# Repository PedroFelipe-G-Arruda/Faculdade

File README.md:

# Faculdade
Matérias e programas desenvolvidos no meu 6° semestre de Engenharia da Computação.

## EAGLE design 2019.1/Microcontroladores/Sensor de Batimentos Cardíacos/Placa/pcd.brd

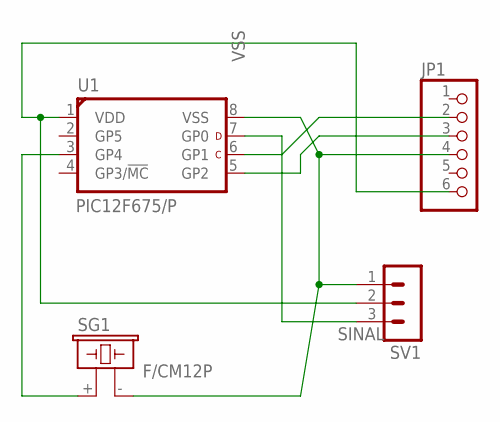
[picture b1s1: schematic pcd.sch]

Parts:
JP1: PINHD-1X6; 1X06
SG1: F/CM12P
SV1: MA03-1
U1: PIC12F675/P; DIL8-P

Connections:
unnamed: JP1.2, U1.6 (GP1)
unnamed: SG1.+ (1), U1.3 (GP4)
unnamed: JP1.3, U1.5 (GP2)
SINAL: SV1.3, U1.7 (GP0)
VDD: JP1.6, SV1.2, U1.1 (VDD)
VSS: JP1.4, SG1.- (2), SV1.1, U1.8 (VSS)

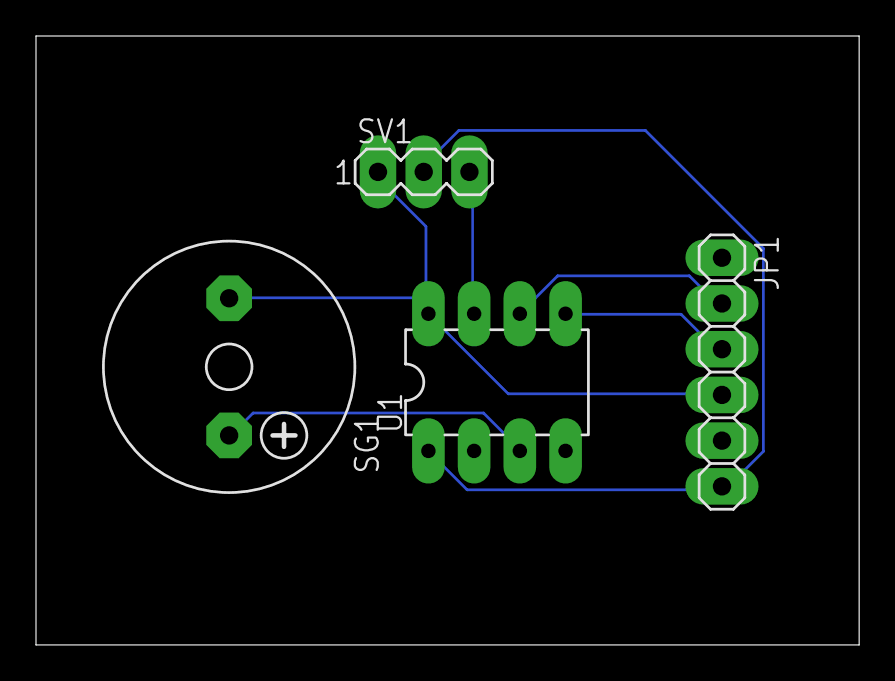
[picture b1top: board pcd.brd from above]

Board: 2 copper layers, 45.7 x 33.8 mm, 4 parts (0 on the bottom side), 6 nets.

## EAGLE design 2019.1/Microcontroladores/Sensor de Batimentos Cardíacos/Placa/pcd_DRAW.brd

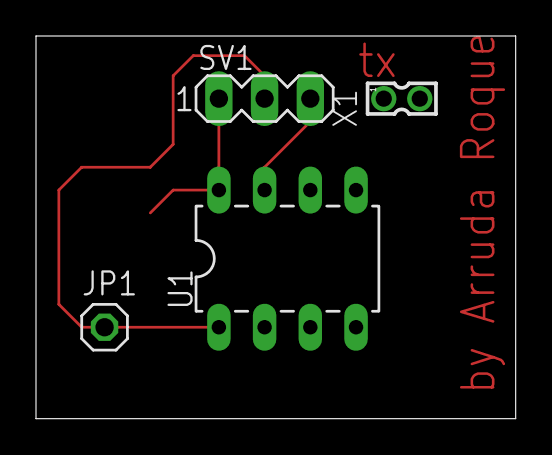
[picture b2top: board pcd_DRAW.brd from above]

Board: 2 copper layers, 26.6 x 21.3 mm, 4 parts (0 on the bottom side), 5 nets.

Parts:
JP1: 1X01
SV1: MA03-1
U1: PIC12F675/P; DIL8-P
X1: 87758-0216

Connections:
unnamed: U1.6, X1.1
unnamed: U1.5, X1.2
SINAL: SV1.3, U1.7
VDD: JP1.1, SV1.2, U1.1
VSS: SV1.1, U1.8

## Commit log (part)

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2018-08-14 Primeira tarefa
2018-08-14 Test
2018-08-14 Update programa01.py
    Programa que lê nomes de coloca em um arquivo de texto.
2018-08-14 Programa pronto
2018-08-14 Update README.md
    Estudande
2018-08-14 Aquivo com os nomes
2018-08-14 troca de nome do aquivo
2018-08-14 Atividades
2018-08-14 Nomes
2018-08-14 Programa conta linhas
2018-08-15 Programa fucionando mas não finalizado
2018-08-17 no message
2018-08-20 Não esta funcionando
2018-08-23 Programa Finalizado
2018-08-23 PRograma Automatos finalizado
2018-08-25 Rpgrama Finalizado
2018-09-05 Create LICENSE
2018-09-05 Gramatica
2018-09-12 Gramatica da linguagem 2
2018-09-12 Nova estrutura do FOR
2018-09-25 Programa usado na geração da gramatica
2018-09-25 Programa usado para fazer grafos
2018-10-12 Pronto ou quase
2018-10-13 Codigo finalizado
2018-10-26 Material LP2
2018-11-04 Analizador Lexico Finalizado
2018-11-04 Analizador Semantico Finalizado
2018-11-05 Analizador Sintatico Finalizado
2018-12-15 Codigo intermetiario/quase
2018-12-16 assembly 10%
2018-12-17 Rodando 98%
2019-02-26 Novo Semestre
2019-05-25 Bump tar from 2.2.1 to 2.2.2 in /2019.1/LP3/Ionic/Iapp01
    Bumps [tar](https://github.com/npm/node-tar) from 2.2.1 to 2.2.2.
    - [Release notes](https://github.com/npm/node-tar/releases)
    - [Commits](https://github.com/npm/node-tar/compare/v2.2.1...v2.2.2)
2019-05-31 Bump fstream from 1.0.11 to 1.0.12 in /2019.1/LP3/Ionic/Iapp01
    Bumps [fstream](https://github.com/npm/fstream) from 1.0.11 to 1.0.12.
    - [Release notes](https://github.com/npm/fstream/releases)
    - [Commits](https://github.com/npm/fstream/compare/v1.0.11...v1.0.12)
2019-12-29 Bump handlebars in /2019.1/LP3/Angular/my-project-name
    Bumps [handlebars](https://github.com/wycats/handlebars.js) from 4.1.2 to 4.5.3.
    - [Release notes](https://github.com/wycats/handlebars.js/releases)
    - [Changelog](https://github.com/wycats/handlebars.js/blob/master/release-notes.md)
    - [Commits](https://github.com/wycats/handlebars.js/compare/v4.1.2...v4.5.3)
2020-03-15 Bump acorn from 6.1.1 to 6.4.1 in /2019.1/LP3/Angular/my-project-name
    Bumps [acorn](https://github.com/acornjs/acorn) from 6.1.1 to 6.4.1.
    - [Release notes](https://github.com/acornjs/acorn/releases)
    - [Commits](https://github.com/acornjs/acorn/compare/6.1.1...6.4.1)
2020-06-07 Bump websocket-extensions in /2019.1/LP3/Angular/my-project-name
    Bumps [websocket-extensions](https://github.com/faye/websocket-extensions-node) from 0.1.3 to 0.1.4.
    - [Release notes](https://github.com/faye/websocket-extensions-node/releases)
    - [Changelog](https://github.com/faye/websocket-extensions-node/blob/master/CHANGELOG.md)
    - [Commits](https://github.com/faye/websocket-extensions-node/compare/0.1.3...0.1.4)
2020-07-07 Bump mixin-deep in /2019.1/LP3/Angular/my-project-name
    Bumps [mixin-deep](https://github.com/jonschlinkert/mixin-deep) from 1.3.1 to 1.3.2.
    - [Release notes](https://github.com/jonschlinkert/mixin-deep/releases)
    - [Commits](https://github.com/jonschlinkert/mixin-deep/compare/1.3.1...1.3.2)
2020-07-31 Bump elliptic from 6.4.1 to 6.5.3 in /2019.1/LP3/Angular/my-project-name
    Bumps [elliptic](https://github.com/indutny/elliptic) from 6.4.1 to 6.5.3.
    - [Release notes](https://github.com/indutny/elliptic/releases)
    - [Commits](https://github.com/indutny/elliptic/compare/v6.4.1...v6.5.3)
2020-09-10 Bump http-proxy in /2019.1/LP3/Angular/my-project-name
    Bumps [http-proxy](https://github.com/http-party/node-http-proxy) from 1.17.0 to 1.18.1.
    - [Release notes](https://github.com/http-party/node-http-proxy/releases)
    - [Changelog](https://github.com/http-party/node-http-proxy/blob/master/CHANGELOG.md)
    - [Commits](https://github.com/http-party/node-http-proxy/compare/1.17.0...1.18.1)
2021-03-30 Bump y18n from 4.0.0 to 4.0.1 in /2019.1/LP3/Angular/my-project-name
    Bumps [y18n](https://github.com/yargs/y18n) from 4.0.0 to 4.0.1.
    - [Release notes](https://github.com/yargs/y18n/releases)
    - [Changelog](https://github.com/yargs/y18n/blob/master/CHANGELOG.md)
    - [Commits](https://github.com/yargs/y18n/commits)
2021-04-30 Bump ssri from 6.0.1 to 6.0.2 in /2019.1/LP3/Angular/my-project-name
    Bumps [ssri](https://github.com/npm/ssri) from 6.0.1 to 6.0.2.
    - [Release notes](https://github.com/npm/ssri/releases)
    - [Changelog](https://github.com/npm/ssri/blob/v6.0.2/CHANGELOG.md)
    - [Commits](https://github.com/npm/ssri/compare/v6.0.1...v6.0.2)
2021-05-08 Bump url-parse in /2019.1/LP3/Angular/my-project-name
    Bumps [url-parse](https://github.com/unshiftio/url-parse) from 1.4.7 to 1.5.1.
    - [Release notes](https://github.com/unshiftio/url-parse/releases)
    - [Commits](https://github.com/unshiftio/url-parse/compare/1.4.7...1.5.1)
2021-05-09 Bump lodash in /2019.1/LP3/Angular/my-project-name
    Bumps [lodash](https://github.com/lodash/lodash) from 4.17.19 to 4.17.21.
    - [Release notes](https://github.com/lodash/lodash/releases)
    - [Commits](https://github.com/lodash/lodash/compare/4.17.19...4.17.21)
2021-05-27 Bump dns-packet in /2019.1/LP3/Angular/my-project-name
    Bumps [dns-packet](https://github.com/mafintosh/dns-packet) from 1.3.1 to 1.3.4.
    - [Release notes](https://github.com/mafintosh/dns-packet/releases)
    - [Changelog](https://github.com/mafintosh/dns-packet/blob/master/CHANGELOG.md)
    - [Commits](https://github.com/mafintosh/dns-packet/compare/v1.3.1...v1.3.4)
2021-08-04 Bump tar from 4.4.8 to 4.4.15 in /2019.1/LP3/Angular/my-project-name
    Bumps [tar](https://github.com/npm/node-tar) from 4.4.8 to 4.4.15.
    - [Release notes](https://github.com/npm/node-tar/releases)
    - [Changelog](https://github.com/npm/node-tar/blob/main/CHANGELOG.md)
    - [Commits](https://github.com/npm/node-tar/compare/v4.4.8...v4.4.15)
    ---
    updated-dependencies:
2021-09-01 Bump tar from 4.4.8 to 4.4.19 in /2019.1/LP3/Angular/my-project-name
    Bumps [tar](https://github.com/npm/node-tar) from 4.4.8 to 4.4.19.
    - [Release notes](https://github.com/npm/node-tar/releases)
    - [Changelog](https://github.com/npm/node-tar/blob/main/CHANGELOG.md)
    - [Commits](https://github.com/npm/node-tar/compare/v4.4.8...v4.4.19)
    ---
    updated-dependencies:
2021-10-06 Bump url-parse in /2019.1/LP3/Angular/my-project-name
    Bumps [url-parse](https://github.com/unshiftio/url-parse) from 1.4.7 to 1.5.3.
    - [Release notes](https://github.com/unshiftio/url-parse/releases)
    - [Commits](https://github.com/unshiftio/url-parse/compare/1.4.7...1.5.3)
    ---
    updated-dependencies:
    - dependency-name: url-parse
2022-01-15 Bump shelljs from 0.8.3 to 0.8.5 in /2019.1/LP3/Angular/my-project-name
    Bumps [shelljs](https://github.com/shelljs/shelljs) from 0.8.3 to 0.8.5.
    - [Release notes](https://github.com/shelljs/shelljs/releases)
    - [Changelog](https://github.com/shelljs/shelljs/blob/master/CHANGELOG.md)
    - [Commits](https://github.com/shelljs/shelljs/compare/v0.8.3...v0.8.5)
    ---
    updated-dependencies:
2022-02-11 Bump karma from 4.1.0 to 6.3.14 in /2019.1/LP3/Angular/my-project-name
    Bumps [karma](https://github.com/karma-runner/karma) from 4.1.0 to 6.3.14.
    - [Release notes](https://github.com/karma-runner/karma/releases)
    - [Changelog](https://github.com/karma-runner/karma/blob/master/CHANGELOG.md)
    - [Commits](https://github.com/karma-runner/karma/compare/v4.1.0...v6.3.14)
    ---
    updated-dependencies:
2022-02-18 Bump url-parse in /2019.1/LP3/Angular/my-project-name
    Bumps [url-parse](https://github.com/unshiftio/url-parse) from 1.4.7 to 1.5.7.
    - [Release notes](https://github.com/unshiftio/url-parse/releases)
    - [Commits](https://github.com/unshiftio/url-parse/compare/1.4.7...1.5.7)
    ---
    updated-dependencies:
    - dependency-name: url-parse
2022-02-26 Bump url-parse in /2019.1/LP3/Angular/my-project-name
    Bumps [url-parse](https://github.com/unshiftio/url-parse) from 1.4.7 to 1.5.10.
    - [Release notes](https://github.com/unshiftio/url-parse/releases)
    - [Commits](https://github.com/unshiftio/url-parse/compare/1.4.7...1.5.10)
    ---
    updated-dependencies:
    - dependency-name: url-parse
2022-06-01 Bump eventsource in /2019.1/LP3/Angular/my-project-name
    Bumps [eventsource](https://github.com/EventSource/eventsource) from 1.0.7 to 1.1.1.
    - [Release notes](https://github.com/EventSource/eventsource/releases)
    - [Changelog](https://github.com/EventSource/eventsource/blob/master/HISTORY.md)
    - [Commits](https://github.com/EventSource/eventsource/compare/v1.0.7...v1.1.1)
    ---
    updated-dependencies:
2022-06-02 Bump @angular/core in /2019.1/LP3/Angular/my-project-name
    Bumps [@angular/core](https://github.com/angular/angular/tree/HEAD/packages/core) from 8.0.0 to 11.0.5.
    - [Release notes](https://github.com/angular/angular/releases)
    - [Changelog](https://github.com/angular/angular/blob/main/CHANGELOG.md)
    - [Commits](https://github.com/angular/angular/commits/11.0.5/packages/core)
    ---
    updated-dependencies:
2022-11-18 Bump loader-utils and @angular-devkit/build-angular
    Bumps [loader-utils](https://github.com/webpack/loader-utils) to 3.2.1 and updates ancestor dependency [@angular-devkit/build-angular](https://github.com/angular/angular-cli). These dependencies need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
    Updates `loader-utils` from 1.2.3 to 3.2.1
    - [Release notes](https://github.com/webpack/loader-utils/releases)
    - [Changelog](https://github.com/webpack/loader-utils/blob/master/CHANGELOG.md)
    - [Commits](https://github.com/webpack/loader-utils/compare/v1.2.3...v3.2.1)
    Updates `@angular-devkit/build-angular` from 0.800.2 to 15.0.0
2022-11-23 Bump engine.io and karma in /2019.1/LP3/Angular/my-project-name
    Bumps [engine.io](https://github.com/socketio/engine.io) to 6.2.1 and updates ancestor dependency [karma](https://github.com/karma-runner/karma). These dependencies need to be updated together.
    Updates `engine.io` from 3.2.1 to 6.2.1
    - [Release notes](https://github.com/socketio/engine.io/releases)
    - [Changelog](https://github.com/socketio/engine.io/blob/main/CHANGELOG.md)
    - [Commits](https://github.com/socketio/engine.io/compare/3.2.1...6.2.1)
    Updates `karma` from 4.1.0 to 6.4.1
2022-12-09 Bump qs from 6.5.2 to 6.5.3 in /2019.1/LP3/Angular/my-project-name
    Bumps [qs](https://github.com/ljharb/qs) from 6.5.2 to 6.5.3.
    - [Release notes](https://github.com/ljharb/qs/releases)
    - [Changelog](https://github.com/ljharb/qs/blob/main/CHANGELOG.md)
    - [Commits](https://github.com/ljharb/qs/compare/v6.5.2...v6.5.3)
    ---
    updated-dependencies:
2022-12-10 Bump express in /2019.1/LP3/Angular/my-project-name
    Bumps [express](https://github.com/expressjs/express) from 4.17.1 to 4.18.2.
    - [Release notes](https://github.com/expressjs/express/releases)
    - [Changelog](https://github.com/expressjs/express/blob/master/History.md)
    - [Commits](https://github.com/expressjs/express/compare/4.17.1...4.18.2)
    ---
    updated-dependencies:
2023-01-07 Bump json5 from 1.0.1 to 1.0.2 in /2019.1/LP3/Angular/my-project-name
    Bumps [json5](https://github.com/json5/json5) from 1.0.1 to 1.0.2.
    - [Release notes](https://github.com/json5/json5/releases)
    - [Changelog](https://github.com/json5/json5/blob/main/CHANGELOG.md)
    - [Commits](https://github.com/json5/json5/compare/v1.0.1...v1.0.2)
    ---
    updated-dependencies:
